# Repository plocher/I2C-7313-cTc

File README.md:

# I2C-7313-cTc
## License: CERN Open Hardware Licence v1.2

I2C MAX7313-based IO Expander cTc Wiring Harness

Simple PCBs to help with taming the wiring ratsnest found behind a CTC machine's panels by concentrating the majority of LEDs and Switches directly on a PCB.

The [I2C-8574-cTc](/pages/I2C-8574-cTc.html) versions are simple wiring-to-I2C adapters, these 2.1 versions are mounting plates for switches and LEDs as well.

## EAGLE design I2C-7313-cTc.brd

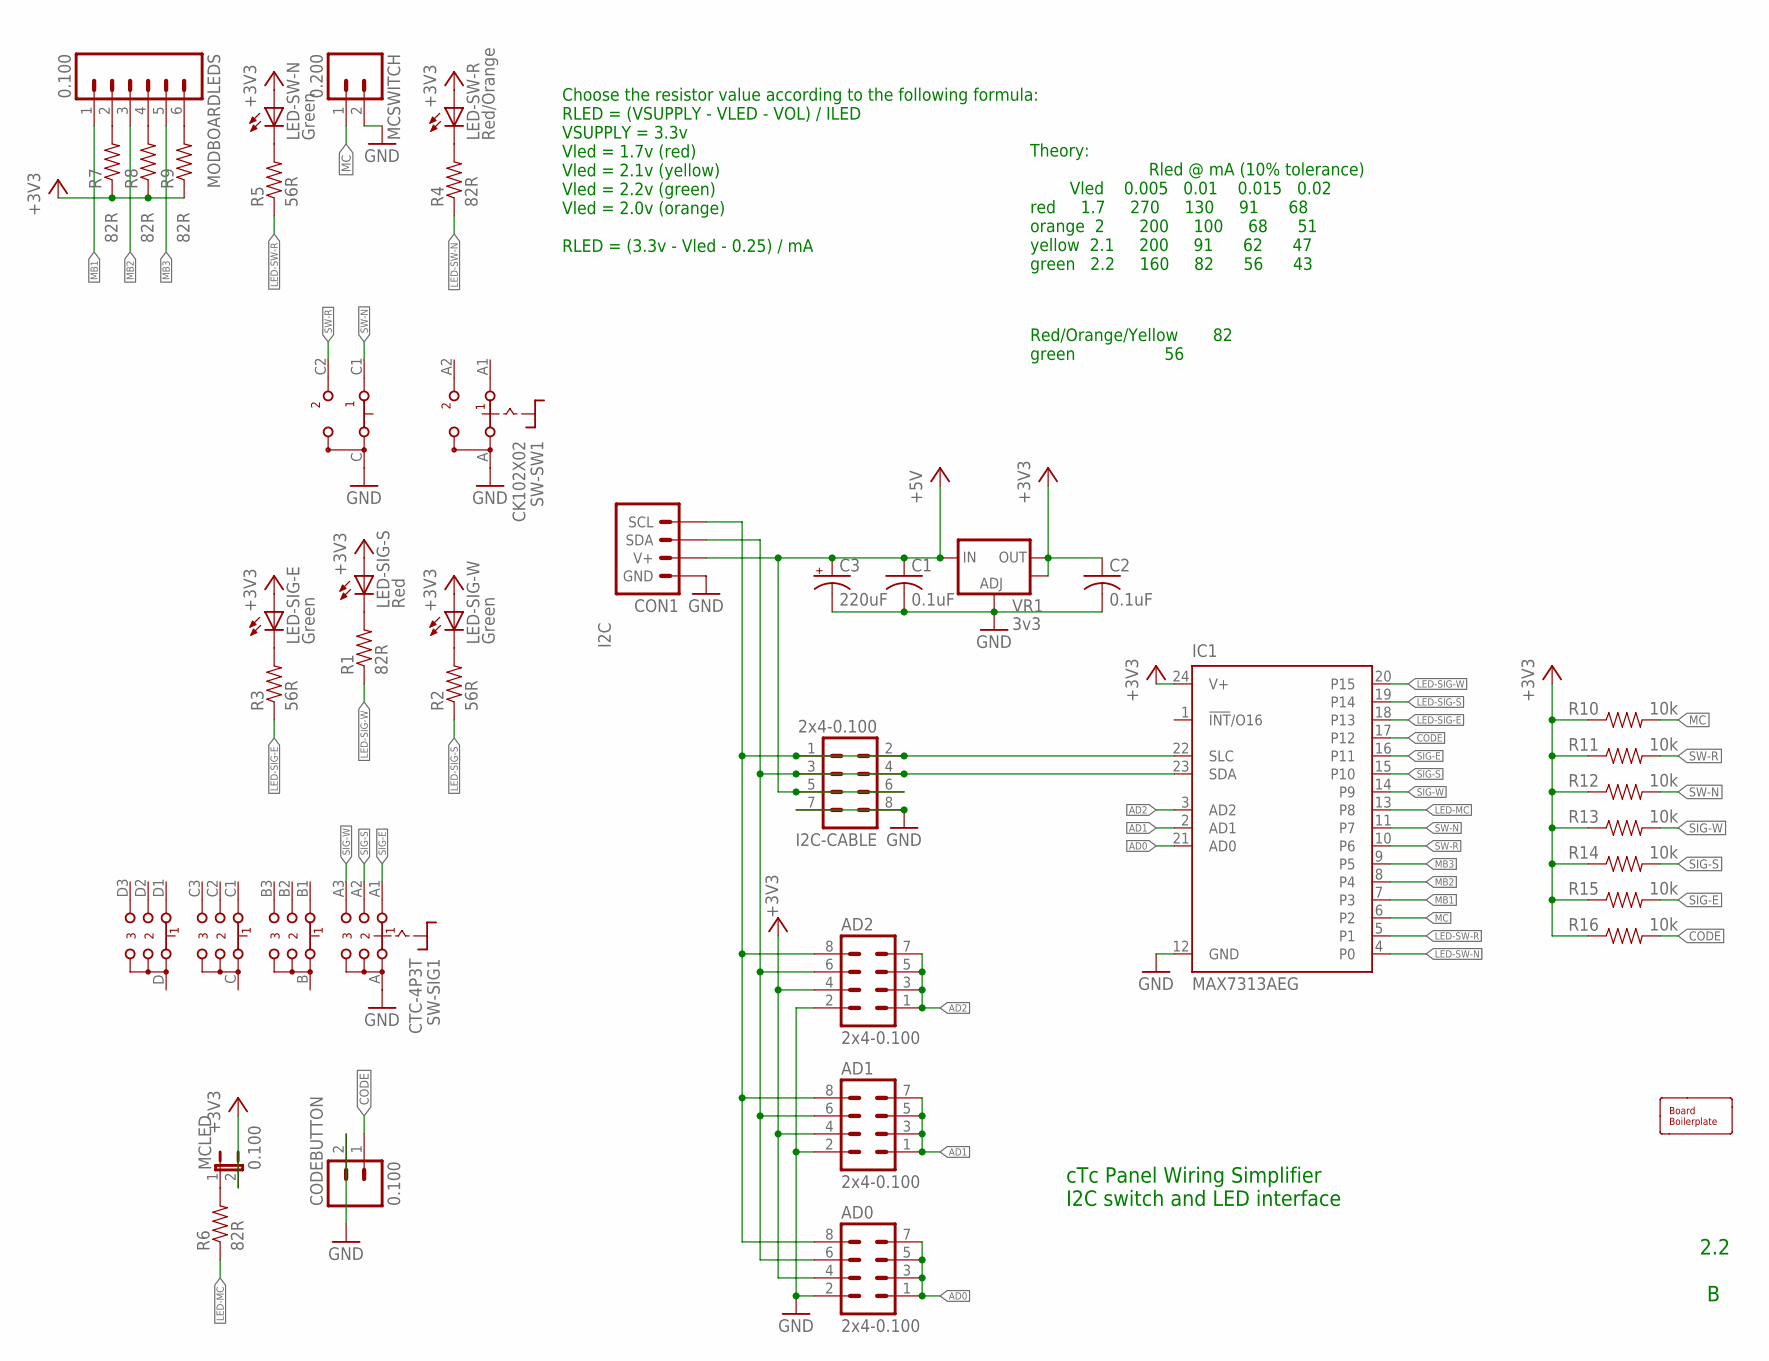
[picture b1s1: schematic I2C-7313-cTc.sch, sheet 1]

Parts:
AD0, AD1, AD2: 2x4-0.100; MA04-2
BOARD1: BOARD; BOARD-SEEED10X15/2-NOHOLES
C1, C2: 0.1uF; 0603-CAP
C3: 220uF; 0810-CAP
CODEBUTTON: 0.100; 1X02_LOCK
CON1: I2C; I2C-L
I2C-CABLE: 2x4-0.100; MA04-2
IC1: MAX7313AEG; QSOP24
LED-SIG-E: Green; LED3MM
LED-SIG-S: Red; LED3MM
LED-SIG-W: Green; LED3MM
LED-SW-N: Green; LED3MM
LED-SW-R: Red/Orange; LED3MM
MCLED: 0.100; 1X02_LOCK
MCSWITCH: 0.200; SCREWTERMINAL-5MM-2
MODBOARDLEDS: 0.100; 1X06_LOCK_LONGPADS
R1, R4, R6, R7, R8, R9: 82R; 0603-RES
R2, R3, R5: 56R; 0603-RES
R10, R11, R12, R13, R14, R15, R16: 10k; 0603-RES
SW-SIG1: CTC-4P3T
SW-SW1: CK102X02
VR1: 3v3; SOT223

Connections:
+3V3: AD0.4, AD1.4, AD2.4, C2.1, IC1.24 (V+), LED-SIG-E.A, LED-SIG-S.A, LED-SIG-W.A, LED-SW-N.A, LED-SW-R.A, MCLED.2, R7.1, R8.1, R9.1, R10.1, R11.1, R12.1, R13.1, R14.1, R15.1, R16.1, VR1.2 (OUT), VR1.4 (OUT); also elsewhere on the board
+5V: C1.1, C3.+, CON1.V+, CON1.V+@1 (V+), I2C-CABLE.5, I2C-CABLE.6, VR1.3 (IN); also elsewhere on the board
AD0: AD0.1, AD0.3, AD0.5, AD0.7, IC1.21 (AD0); also elsewhere on the board
AD1: AD1.1, AD1.3, AD1.5, AD1.7, IC1.2 (AD1); also elsewhere on the board
AD2: AD2.1, AD2.3, AD2.5, AD2.7, IC1.3 (AD2); also elsewhere on the board
CODE: CODEBUTTON.1 (A), IC1.17 (P12), R16.2; also elsewhere on the board
GND: AD0.2, AD1.2, AD2.2, C1.2, C2.2, C3.-, CODEBUTTON.2 (B), CON1.GND, CON1.GND@1 (GND), I2C-CABLE.7, I2C-CABLE.8, IC1.12 (GND), MCSWITCH.2 (B), SW-SIG1.A, SW-SW1.A, SW-SW1.C, VR1.1 (ADJ); also elsewhere on the board
LED-MC: IC1.13 (P8), R6.1; also elsewhere on the board
LED-SIG-E: IC1.18 (P13), R3.1; also elsewhere on the board
LED-SIG-S: IC1.19 (P14), R2.1; also elsewhere on the board
LED-SIG-W: IC1.20 (P15), R1.1; also elsewhere on the board
LED-SW-N: IC1.4 (P0), R4.1; also elsewhere on the board
LED-SW-R: IC1.5 (P1), R5.1; also elsewhere on the board
MB1: IC1.7 (P3), MODBOARDLEDS.1; also elsewhere on the board
MB2: IC1.8 (P4), MODBOARDLEDS.3; also elsewhere on the board
MB3: IC1.9 (P5), MODBOARDLEDS.5; also elsewhere on the board
MC: IC1.6 (P2), MCSWITCH.1 (A), R10.2; also elsewhere on the board
unnamed: MCLED.1, R6.2
unnamed: LED-SW-N.K (C), R5.2
unnamed: LED-SW-R.K (C), R4.2
unnamed: MODBOARDLEDS.2, R7.2
unnamed: LED-SIG-E.K (C), R3.2
unnamed: MODBOARDLEDS.4, R8.2
unnamed: MODBOARDLEDS.6, R9.2
unnamed: LED-SIG-W.K (C), R2.2
unnamed: LED-SIG-S.K (C), R1.2
SCL: AD0.8, AD1.8, AD2.8, CON1.SCL, CON1.SCL@1 (SCL), I2C-CABLE.1, I2C-CABLE.2, IC1.22 (SLC)
SDA: AD0.6, AD1.6, AD2.6, CON1.SDA, CON1.SDA@1 (SDA), I2C-CABLE.3, I2C-CABLE.4, IC1.23 (SDA)
SIG-E: IC1.16 (P11), R15.2, SW-SIG1.A1; also elsewhere on the board
SIG-S: IC1.15 (P10), R14.2, SW-SIG1.A2; also elsewhere on the board
SIG-W: IC1.14 (P9), R13.2, SW-SIG1.A3; also elsewhere on the board
SW-N: IC1.11 (P7), R12.2, SW-SW1.C1; also elsewhere on the board
SW-R: IC1.10 (P6), R11.2, SW-SW1.C2; also elsewhere on the board

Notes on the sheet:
Choose the resistor value according to the following formula: RLED = (VSUPPLY - VLED - VOL) / ILED VSUPPLY = 3.3v Vled = 1.7v (red) Vled = 2.1v (yellow) Vled = 2.2v (green) Vled = 2.0v (orange) RLED = (3.3v - Vled - 0.25) / mA
Theory: Rled @ mA (10% tolerance) Vled 0.005 0.01 0.015 0.02 red 1.7 270 130 91 68 orange 2 200 100 68 51 yellow 2.1 200 91 62 47 green 2.2 160 82 56 43
cTc Panel Wiring Simplifier I2C switch and LED interface
2.2
Red/Orange/Yellow 82 green 56

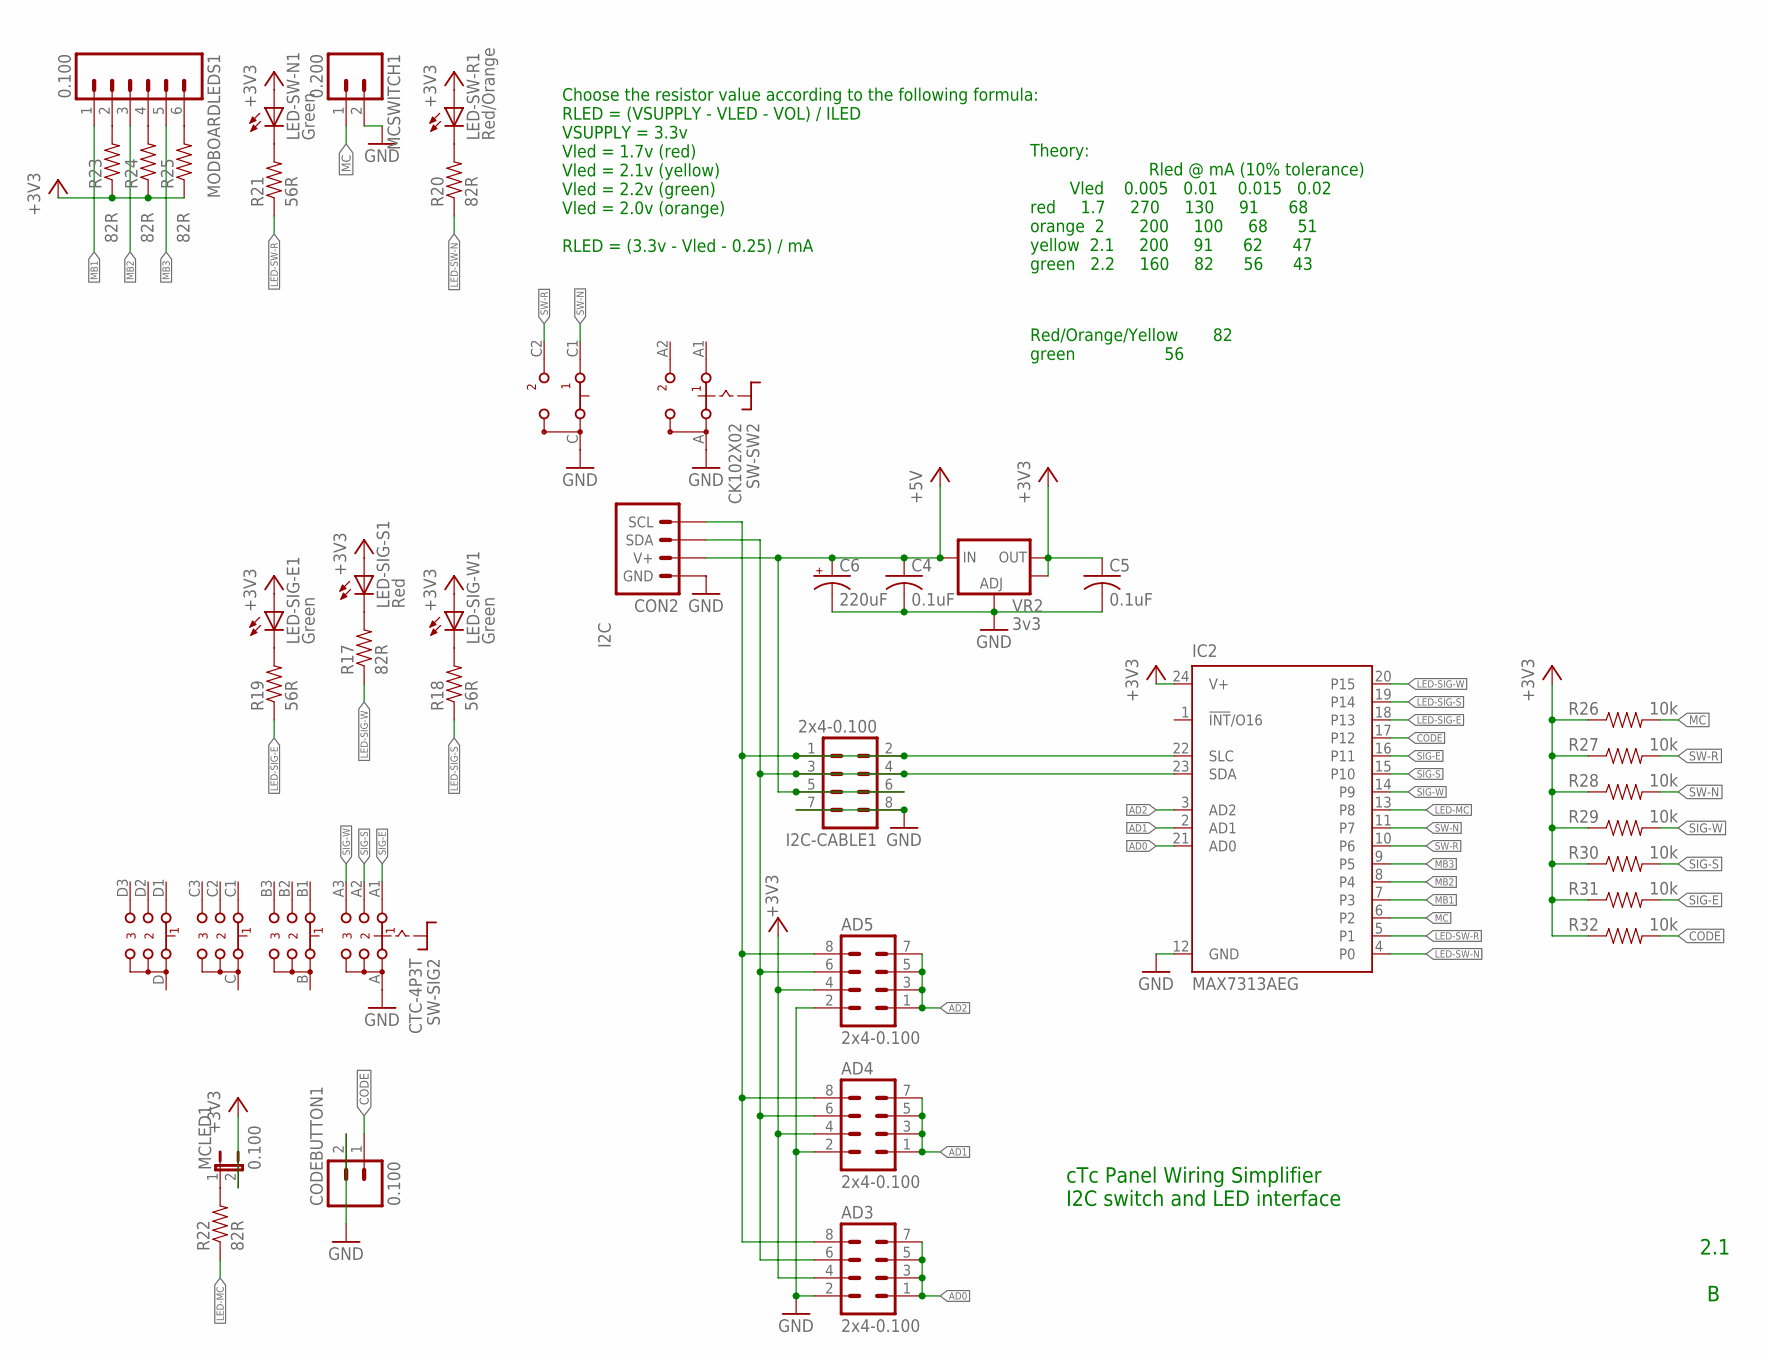
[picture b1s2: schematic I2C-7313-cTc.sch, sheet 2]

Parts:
AD3, AD4, AD5: 2x4-0.100; MA04-2
C4, C5: 0.1uF; 0603-CAP
C6: 220uF; 0810-CAP
CODEBUTTON1: 0.100; 1X02_LOCK
CON2: I2C; I2C-L
I2C-CABLE1: 2x4-0.100; MA04-2
IC2: MAX7313AEG; QSOP24
LED-SIG-E1: Green; LED3MM
LED-SIG-S1: Red; LED3MM
LED-SIG-W1: Green; LED3MM
LED-SW-N1: Green; LED3MM
LED-SW-R1: Red/Orange; LED3MM
MCLED1: 0.100; 1X02_LOCK
MCSWITCH1: 0.200; SCREWTERMINAL-5MM-2
MODBOARDLEDS1: 0.100; 1X06_LOCK_LONGPADS
R17, R20, R22, R23, R24, R25: 82R; 0603-RES
R18, R19, R21: 56R; 0603-RES
R26, R27, R28, R29, R30, R31, R32: 10k; 0603-RES
SW-SIG2: CTC-4P3T
SW-SW2: CK102X02
VR2: 3v3; SOT223

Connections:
+3V3: AD3.4, AD4.4, AD5.4, C5.1, IC2.24 (V+), LED-SIG-E1.A, LED-SIG-S1.A, LED-SIG-W1.A, LED-SW-N1.A, LED-SW-R1.A, MCLED1.2, R23.1, R24.1, R25.1, R26.1, R27.1, R28.1, R29.1, R30.1, R31.1, R32.1, VR2.2 (OUT), VR2.4 (OUT); also elsewhere on the board
+5V: C4.1, C6.+, CON2.V+, CON2.V+@1 (V+), I2C-CABLE1.5, I2C-CABLE1.6, VR2.3 (IN); also elsewhere on the board
AD0: AD3.1, AD3.3, AD3.5, AD3.7, IC2.21 (AD0); also elsewhere on the board
AD1: AD4.1, AD4.3, AD4.5, AD4.7, IC2.2 (AD1); also elsewhere on the board
AD2: AD5.1, AD5.3, AD5.5, AD5.7, IC2.3 (AD2); also elsewhere on the board
CODE: CODEBUTTON1.1 (A), IC2.17 (P12), R32.2; also elsewhere on the board
GND: AD3.2, AD4.2, AD5.2, C4.2, C5.2, C6.-, CODEBUTTON1.2 (B), CON2.GND, CON2.GND@1 (GND), I2C-CABLE1.7, I2C-CABLE1.8, IC2.12 (GND), MCSWITCH1.2 (B), SW-SIG2.A, SW-SW2.A, SW-SW2.C, VR2.1 (ADJ); also elsewhere on the board
LED-MC: IC2.13 (P8), R22.1; also elsewhere on the board
LED-SIG-E: IC2.18 (P13), R19.1; also elsewhere on the board
LED-SIG-S: IC2.19 (P14), R18.1; also elsewhere on the board
LED-SIG-W: IC2.20 (P15), R17.1; also elsewhere on the board
LED-SW-N: IC2.4 (P0), R20.1; also elsewhere on the board
LED-SW-R: IC2.5 (P1), R21.1; also elsewhere on the board
MB1: IC2.7 (P3), MODBOARDLEDS1.1; also elsewhere on the board
MB2: IC2.8 (P4), MODBOARDLEDS1.3; also elsewhere on the board
MB3: IC2.9 (P5), MODBOARDLEDS1.5; also elsewhere on the board
MC: IC2.6 (P2), MCSWITCH1.1 (A), R26.2; also elsewhere on the board
unnamed: MCLED1.1, R22.2
unnamed: MODBOARDLEDS1.2, R23.2
unnamed: MODBOARDLEDS1.4, R24.2
unnamed: MODBOARDLEDS1.6, R25.2
unnamed: LED-SW-N1.K (C), R21.2
unnamed: LED-SW-R1.K (C), R20.2
unnamed: LED-SIG-E1.K (C), R19.2
unnamed: LED-SIG-W1.K (C), R18.2
unnamed: LED-SIG-S1.K (C), R17.2
SCL1: AD3.8, AD4.8, AD5.8, CON2.SCL, CON2.SCL@1 (SCL), I2C-CABLE1.1, I2C-CABLE1.2, IC2.22 (SLC)
SDA1: AD3.6, AD4.6, AD5.6, CON2.SDA, CON2.SDA@1 (SDA), I2C-CABLE1.3, I2C-CABLE1.4, IC2.23 (SDA)
SIG-E: IC2.16 (P11), R31.2, SW-SIG2.A1; also elsewhere on the board
SIG-S: IC2.15 (P10), R30.2, SW-SIG2.A2; also elsewhere on the board
SIG-W: IC2.14 (P9), R29.2, SW-SIG2.A3; also elsewhere on the board
SW-N: IC2.11 (P7), R28.2, SW-SW2.C1; also elsewhere on the board
SW-R: IC2.10 (P6), R27.2, SW-SW2.C2; also elsewhere on the board

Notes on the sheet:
Choose the resistor value according to the following formula: RLED = (VSUPPLY - VLED - VOL) / ILED VSUPPLY = 3.3v Vled = 1.7v (red) Vled = 2.1v (yellow) Vled = 2.2v (green) Vled = 2.0v (orange) RLED = (3.3v - Vled - 0.25) / mA
Theory: Rled @ mA (10% tolerance) Vled 0.005 0.01 0.015 0.02 red 1.7 270 130 91 68 orange 2 200 100 68 51 yellow 2.1 200 91 62 47 green 2.2 160 82 56 43
cTc Panel Wiring Simplifier I2C switch and LED interface
2.1
Red/Orange/Yellow 82 green 56

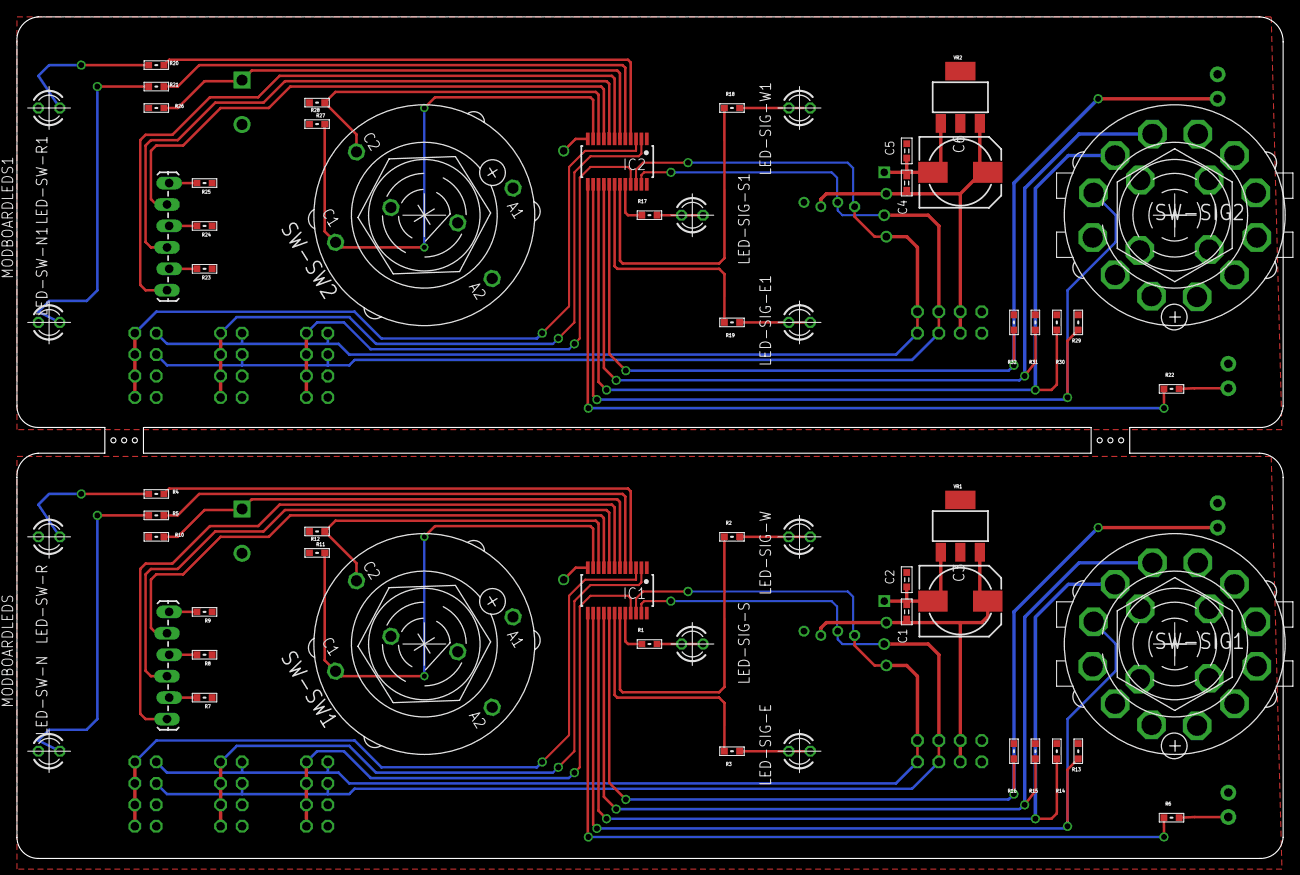
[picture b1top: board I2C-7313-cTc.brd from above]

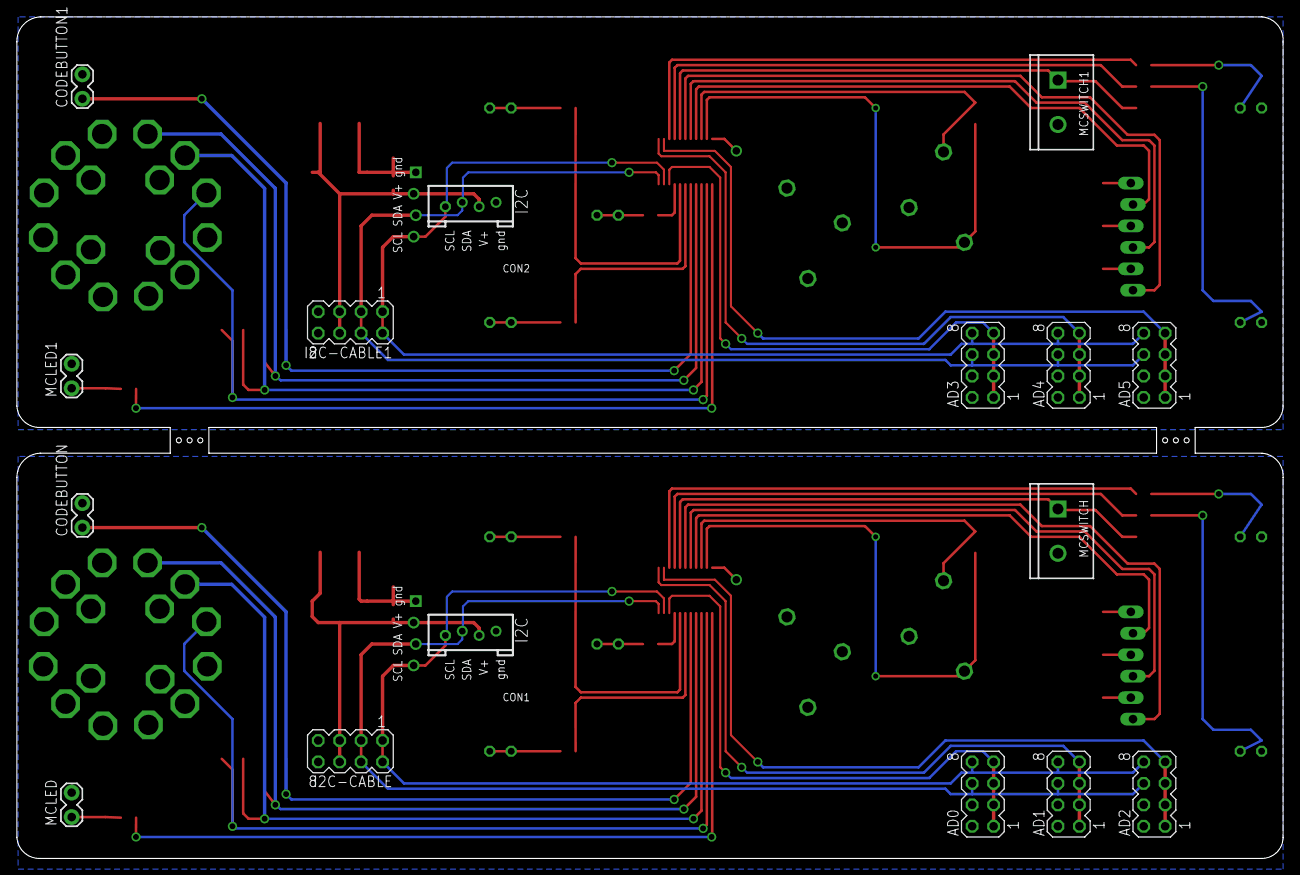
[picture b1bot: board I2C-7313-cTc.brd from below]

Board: 2 copper layers, 150.0 x 99.7 mm, 75 parts (16 on the bottom side), 44 nets.

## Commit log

2019-11-25 2.1-panel
2019-11-27 silence eagle complaints when processing
2020-05-04 updated tags
2020-10-06 normalized values
2020-11-03 replaced 4PDT rotary with 2P2T SR2616F-0202-18F58-D8-N
2020-11-03 Version 2.2
